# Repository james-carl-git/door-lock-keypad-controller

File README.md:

# Replacement Door Lock Combo Keypad Controller
The controller on the Kwikset combo door lock to my house died so instead of buying a new one I did the sensible thing and spent hours designing my own ;)

Features (watch video)
- Low power consumption using MSP430 allow it to run on batteries for months/years
- Easy programming with button
- Combo stored in non-volatile memory so no need to re-program when swapping batteries
- Pizo speaker for audible button presses
- Components are inexpensive and easy to get
- PCB is a small simple 2 layer board I was able to assemble with a hot plate and some solder paste (I have a few spares if interested)
- Mosfet H-bridge to spin lock motor forwards and backwards

https://github.com/james-carl-git/door-lock-keypad-controller/assets/78581339/344f8aa0-f60f-4c66-a90a-e0d3cf9ee638

Notes:
- My lock multiplexes the buttons into 5 connections/wires, they are as follows (You could probably modify the code if your lock is slightly different)
-   Row combos: 1/2 and lock | 3/4 and 5/6 | 7/8 and 9/0
-   Column combos: 1/2 and 3/4 and 7/8 | 5/6 and 9/0 and lock
- I used Energia to program the MSP430, you'll want to put the MSP430 in DIP socket so you can remove it to program it. The PCB does not break out the programing pins
- You're going to want to make sure the voltage regulator(3.3v) has a low quiescent current if you expect the batteries to last
- The combo length is set to 4 in the code but this can be changed to a value up to 16
- PCB designed with EAGLE

Below are pictures of my door lock and original PCB so you can see if maybe this design would work for you. It could also be used for a custom lock project.

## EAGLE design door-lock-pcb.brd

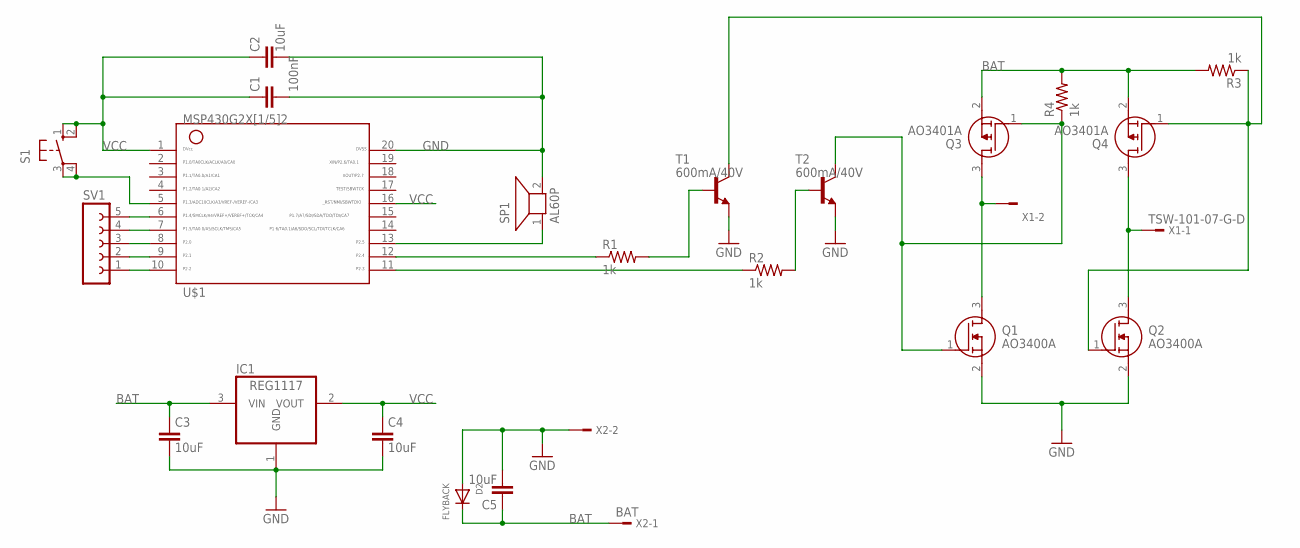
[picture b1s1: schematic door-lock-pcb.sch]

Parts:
C1: 100nF; CAP_0805
C2, C3, C4, C5: 10uF; CAP_0805
D2: FLYBACK; SOD-523
IC1: REG1117; SOT223
Q1, Q2: AO3400A; SOT95P280X125-3N
Q3, Q4: AO3401A; SOT95P280X125-3N
R1, R2, R3, R4: 1k; RES_0805
S1: 10-XX; B3F-10XX
SP1: AL60P
SV1: FE05-1
T1, T2: 600mA/40V; SOT23-3
U$1: G2X[1/5]2---N20; N20
X1: TSW-101-07-G-D; TSW-101-XX-G-D
X2: BAT; TSW-101-XX-G-D

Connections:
BAT: C3.1, C5.1, D2.K (C), IC1.3 (VIN), Q3.2 (S), Q4.2 (S), R3.2, R4.2, X2.1
GND: C1.2, C2.2, C3.2, C4.2, C5.2, D2.A, IC1.1 (GND), Q1.2 (S), Q2.2 (S), SP1.2, T1.2 (E), T2.2 (E), U$1.20, X2.2
unnamed: SV1.1, U$1.10
unnamed: SV1.2, U$1.9
unnamed: SV1.3, U$1.8
unnamed: SV1.4, U$1.7
unnamed: SV1.5, U$1.6
unnamed: SP1.1, U$1.13
unnamed: S1.3, S1.4 (P1), U$1.5
unnamed: Q1.1 (G), Q3.1 (G), R4.1, T2.3 (C)
unnamed: Q2.1 (G), Q4.1 (G), R3.1, T1.3 (C)
unnamed: R1.1, U$1.12
unnamed: R1.2, T1.1 (B)
unnamed: R2.2, T2.1 (B)
unnamed: R2.1, U$1.11
unnamed: Q1.3 (D), Q3.3 (D), X1.2
unnamed: Q2.3 (D), Q4.3 (D), X1.1
VCC: C1.1, C2.1, C4.1, IC1.2 (VOUT), S1.1 (S), S1.2 (S1), U$1.1, U$1.16

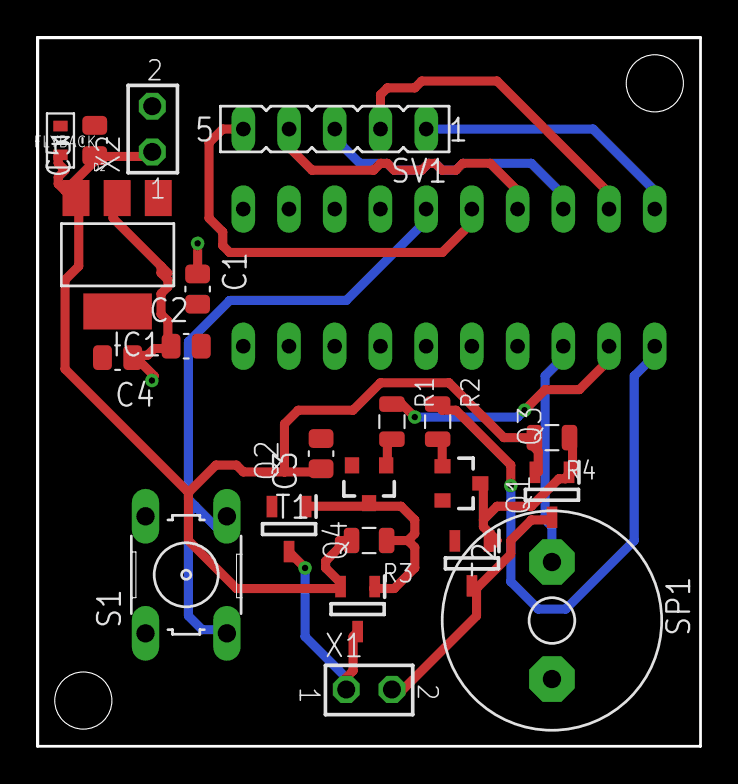
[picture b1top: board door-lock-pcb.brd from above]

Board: 2 copper layers, 36.8 x 39.4 mm, 23 parts (1 on the bottom side), 18 nets.

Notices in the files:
parts and their libraries:
SparkFun-DiscreteSemi: Licensing: Creative Commons ShareAlike 4.0 International - https://creativecommons.org/licenses/by-sa/4.0
